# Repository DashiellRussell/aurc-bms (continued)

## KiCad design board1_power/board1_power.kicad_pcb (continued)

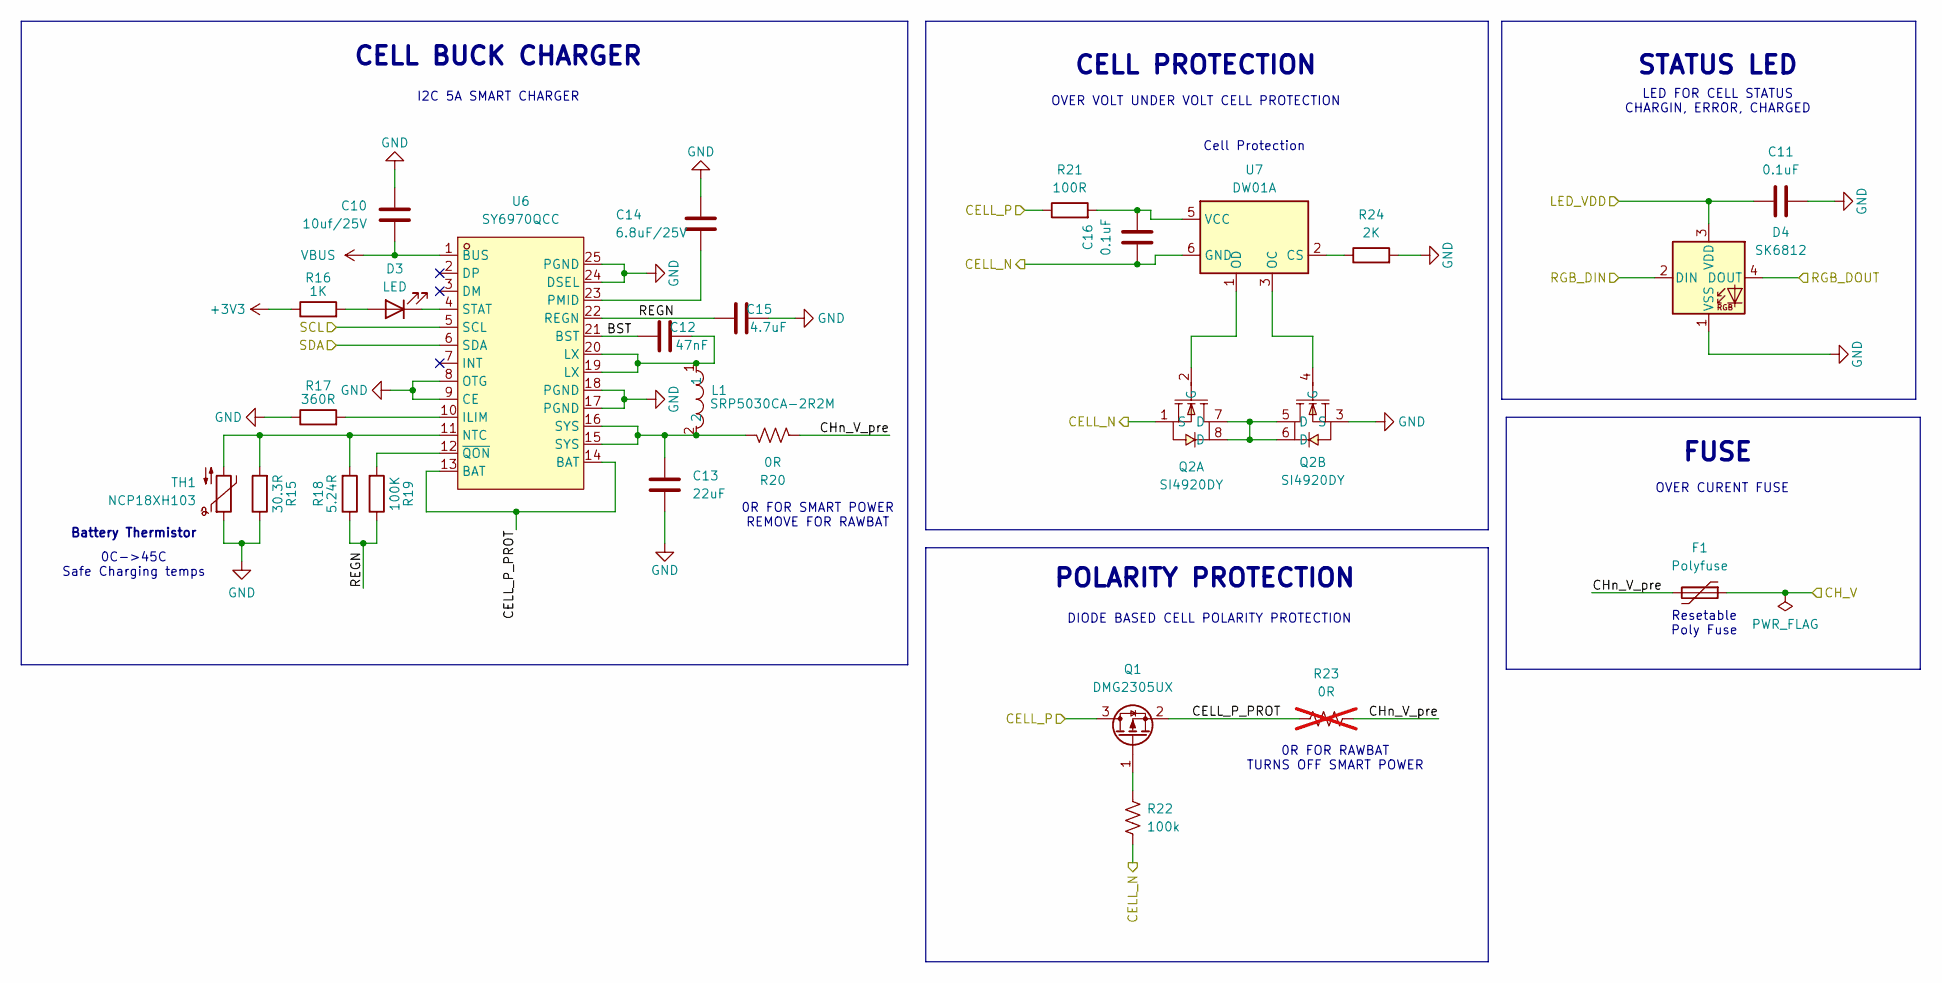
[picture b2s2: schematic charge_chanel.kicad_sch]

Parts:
C10: 10uf/25V; C_1206_3216Metric
C11, C16: 0.1uF; C_0603_1608Metric
C12: 47nF; C_0603_1608Metric
C13: 22uF; C_1206_3216Metric
C14: 6.8uF/25V; C_0805_2012Metric
C15: 4.7uF; C_0805_2012Metric
D3: LED; LED_0603_1608Metric
D4: SK6812; LED_SK6812_PLCC4_5.0x5.0mm_P3.2mm
F1: Polyfuse; Fuse_1812_4532Metric
L1: SRP5030CA-2R2M; IND-SMD_L5.5-W5.3; MPN SRP5030CA-2R2M; LCSC Part C2046809
Q1: DMG2305UX; SOT-23
Q2: SI4920DY; SOIC-8_L4.9-W3.9-P1.27-LS6.2-BL; MPN SI4920DY; LCSC Part C3289759
R15: 30.3R; R_0603_1608Metric
R16: 1K; R_0603_1608Metric
R17: 360R; R_0603_1608Metric
R18: 5.24R; R_0603_1608Metric
R19: 100K; R_0603_1608Metric
R20: 0R; R_2010_5025Metric
R21: 100R; R_0603_1608Metric
R22: 100k; R_0603_1608Metric
R23: 0R; R_2010_5025Metric; not fitted
R24: 2K; R_0603_1608Metric
TH1: NCP18XH103; R_0603_1608Metric
U6: SY6970QCC; QFN-24_L4.0-W4.0-P0.50-TL-EP2.7; MPN SY6970QCC; LCSC Part C5357542
U7: DW01A; SOT-23-6

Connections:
+3V3: R16.1; also elsewhere on the board
/CH1_CN: C16.1, Q2.1 (S), R22.1, U7.6 (GND); also elsewhere on the board
/CH1_CP: Q1.3 (D), R21.1; also elsewhere on the board
/CH1_SCL: U6.5 (SCL); also elsewhere on the board
/CH1_SDA: U6.6 (SDA); also elsewhere on the board
/CH1_V: C11.2, D4.3 (VDD), F1.1; also elsewhere on the board
/Charge_Chanel1 (FC1)/BST: C12.2, U6.21 (BST)
/Charge_Chanel1 (FC1)/CELL_P_PROT: Q1.2 (S), R23.2, U6.13 (BAT), U6.14 (BAT)
/Charge_Chanel1 (FC1)/CHn_V_pre: F1.2, R20.1, R23.1
/Charge_Chanel1 (FC1)/REGN: C15.2, R18.1, R19.1, U6.22 (REGN)
/Charge_Chanel1 (FC1)/RGB_DOUT: D4.4 (DOUT); also elsewhere on the board
/RGB_DATA: D4.2 (DIN); also elsewhere on the board
GND: C10.1, C11.1, C13.2, C14.1, C15.1, D4.1 (VSS), Q2.3 (S), R15.1, R17.1, R24.2, TH1.1, U6.8 (OTG), U6.9 (CE), U6.17 (PGND), U6.18 (PGND), U6.24 (DSEL), U6.25 (PGND); also elsewhere on the board
unnamed: C12.1, L1.1, U6.19 (LX), U6.20 (LX)
unnamed: C13.1, L1.2, R20.2, U6.15 (SYS), U6.16 (SYS)
unnamed: D3.2 (A), R16.2
unnamed: D3.1 (K), U6.4 (STAT)
unnamed: Q1.1 (G), R22.2
unnamed: Q2.5 (D), Q2.6 (D), Q2.7 (D), Q2.8 (D)
unnamed: Q2.2 (G), U7.1 (OD)
unnamed: Q2.4 (G), U7.3 (OC)
unnamed: R17.2, U6.10 (ILIM)
unnamed: R15.2, R18.2, TH1.2, U6.11 (NTC)
unnamed: C14.2, U6.23 (PMID)
unnamed: R19.2, U6.12 (~QON)
unnamed: R24.1, U7.2 (CS)
unnamed: C16.2, R21.2, U7.5 (VCC)
VBUS: C10.2, U6.1 (BUS); also elsewhere on the board

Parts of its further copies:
C17, C24, C31: 10uf/25V; C_1206_3216Metric
C18, C23, C25, C30, C32, C37: 0.1uF; C_0603_1608Metric
C19, C26, C33: 47nF; C_0603_1608Metric
C20, C27, C34: 22uF; C_1206_3216Metric
C21, C28, C35: 6.8uF/25V; C_0805_2012Metric
C22, C29, C36: 4.7uF; C_0805_2012Metric
D5, D7, D9: LED; LED_0603_1608Metric
D6, D8, D10: SK6812; LED_SK6812_PLCC4_5.0x5.0mm_P3.2mm
F2, F3, F4: Polyfuse; Fuse_1812_4532Metric
L2, L3, L4: SRP5030CA-2R2M; IND-SMD_L5.5-W5.3; MPN SRP5030CA-2R2M; LCSC Part C2046809
Q3, Q5, Q7: DMG2305UX; SOT-23
Q4, Q6, Q8: SI4920DY; SOIC-8_L4.9-W3.9-P1.27-LS6.2-BL; MPN SI4920DY; LCSC Part C3289759
R25, R35, R45: 30.3R; R_0603_1608Metric
R26, R36, R46: 1K; R_0603_1608Metric
R27, R37, R47: 360R; R_0603_1608Metric
R28, R38, R48: 5.24R; R_0603_1608Metric
R29, R39, R49: 100K; R_0603_1608Metric
R30, R40, R50: 0R; R_2010_5025Metric
R31, R41, R51: 100R; R_0603_1608Metric
R32, R42, R52: 100k; R_0603_1608Metric
R33, R43, R53: 0R; R_2010_5025Metric; not fitted
R34, R44, R54: 2K; R_0603_1608Metric
TH2, TH3, TH4: NCP18XH103; R_0603_1608Metric
U8, U10, U12: SY6970QCC; QFN-24_L4.0-W4.0-P0.50-TL-EP2.7; MPN SY6970QCC; LCSC Part C5357542
U9, U11, U13: DW01A; SOT-23-6

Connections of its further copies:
+3V3: R26.1, R36.1, R46.1; also elsewhere on the board
/CH1_V: C18.2, C25.2, C32.2, D6.3 (VDD), D8.3 (VDD), D10.3 (VDD); also elsewhere on the board
/CH2_CN: C23.1, Q4.1 (S), R32.1, U9.6 (GND); also elsewhere on the board
/CH2_CP: Q3.3 (D), R31.1; also elsewhere on the board
/CH2_SCL: U8.5 (SCL); also elsewhere on the board
/CH2_SDA: U8.6 (SDA); also elsewhere on the board
/CH2_V: F2.1; also elsewhere on the board
/CH3_CN: C30.1, Q6.1 (S), R42.1, U11.6 (GND); also elsewhere on the board
/CH3_CP: Q5.3 (D), R41.1; also elsewhere on the board
/CH3_SCL: U10.5 (SCL); also elsewhere on the board
/CH3_SDA: U10.6 (SDA); also elsewhere on the board
/CH3_V: F3.1; also elsewhere on the board
/CH4_CN: C37.1, Q8.1 (S), R52.1, U13.6 (GND); also elsewhere on the board
/CH4_CP: Q7.3 (D), R51.1; also elsewhere on the board
/CH4_SCL: U12.5 (SCL); also elsewhere on the board
/CH4_SDA: U12.6 (SDA); also elsewhere on the board
/CH4_V: F4.1; also elsewhere on the board
/Charge_Chanel1 (FC1)/RGB_DOUT: D6.2 (DIN); also elsewhere on the board
/Charge_Chanel2 (FC2)/BST: C19.2, U8.21 (BST)
/Charge_Chanel2 (FC2)/CELL_P_PROT: Q3.2 (S), R33.2, U8.13 (BAT), U8.14 (BAT)
/Charge_Chanel2 (FC2)/CHn_V_pre: F2.2, R30.1, R33.1
/Charge_Chanel2 (FC2)/REGN: C22.2, R28.1, R29.1, U8.22 (REGN)
/Charge_Chanel2 (FC2)/RGB_DOUT: D6.4 (DOUT), D8.2 (DIN)
/Charge_Chanel3(PYRO1)/BST: C26.2, U10.21 (BST)
/Charge_Chanel3(PYRO1)/CELL_P_PROT: Q5.2 (S), R43.2, U10.13 (BAT), U10.14 (BAT)
/Charge_Chanel3(PYRO1)/CHn_V_pre: F3.2, R40.1, R43.1
/Charge_Chanel3(PYRO1)/REGN: C29.2, R38.1, R39.1, U10.22 (REGN)
/Charge_Chanel3(PYRO1)/RGB_DOUT: D8.4 (DOUT), D10.2 (DIN)
/Charge_Chanel4(PYRO2)/BST: C33.2, U12.21 (BST)
/Charge_Chanel4(PYRO2)/CELL_P_PROT: Q7.2 (S), R53.2, U12.13 (BAT), U12.14 (BAT)
/Charge_Chanel4(PYRO2)/CHn_V_pre: F4.2, R50.1, R53.1
/Charge_Chanel4(PYRO2)/REGN: C36.2, R48.1, R49.1, U12.22 (REGN)
/Charge_Chanel4(PYRO2)/RGB_DOUT: D10.4 (DOUT)
GND: C17.1, C18.1, C20.2, C21.1, C22.1, C24.1, C25.1, C27.2, C28.1, C29.1, C31.1, C32.1, C34.2, C35.1, C36.1, D6.1 (VSS), D8.1 (VSS), D10.1 (VSS), Q4.3 (S), Q6.3 (S), Q8.3 (S), R25.1, R27.1, R34.2, R35.1, R37.1, R44.2, R45.1, R47.1, R54.2, TH2.1, TH3.1, TH4.1, U8.8 (OTG), U8.9 (CE), U8.17 (PGND), U8.18 (PGND), U8.24 (DSEL), U8.25 (PGND), U10.8 (OTG), U10.9 (CE), U10.17 (PGND), U10.18 (PGND), U10.24 (DSEL), U10.25 (PGND), U12.8 (OTG), U12.9 (CE), U12.17 (PGND), U12.18 (PGND), U12.24 (DSEL), U12.25 (PGND); also elsewhere on the board
unnamed: C19.1, L2.1, U8.19 (LX), U8.20 (LX)
unnamed: C20.1, L2.2, R30.2, U8.15 (SYS), U8.16 (SYS)
unnamed: C26.1, L3.1, U10.19 (LX), U10.20 (LX)
unnamed: C27.1, L3.2, R40.2, U10.15 (SYS), U10.16 (SYS)
unnamed: C33.1, L4.1, U12.19 (LX), U12.20 (LX)
unnamed: C34.1, L4.2, R50.2, U12.15 (SYS), U12.16 (SYS)
unnamed: D5.2 (A), R26.2
unnamed: D5.1 (K), U8.4 (STAT)
unnamed: D7.2 (A), R36.2
unnamed: D7.1 (K), U10.4 (STAT)
unnamed: D9.2 (A), R46.2
unnamed: D9.1 (K), U12.4 (STAT)
unnamed: Q3.1 (G), R32.2
unnamed: Q4.5 (D), Q4.6 (D), Q4.7 (D), Q4.8 (D)
unnamed: Q4.2 (G), U9.1 (OD)
unnamed: Q4.4 (G), U9.3 (OC)
unnamed: Q5.1 (G), R42.2
unnamed: Q6.5 (D), Q6.6 (D), Q6.7 (D), Q6.8 (D)
unnamed: Q6.2 (G), U11.1 (OD)
unnamed: Q6.4 (G), U11.3 (OC)
unnamed: Q7.1 (G), R52.2
unnamed: Q8.5 (D), Q8.6 (D), Q8.7 (D), Q8.8 (D)
unnamed: Q8.2 (G), U13.1 (OD)
unnamed: Q8.4 (G), U13.3 (OC)
unnamed: R27.2, U8.10 (ILIM)
unnamed: R25.2, R28.2, TH2.2, U8.11 (NTC)
unnamed: C21.2, U8.23 (PMID)
unnamed: R29.2, U8.12 (~QON)
unnamed: R34.1, U9.2 (CS)
unnamed: C23.2, R31.2, U9.5 (VCC)
unnamed: R37.2, U10.10 (ILIM)
unnamed: R35.2, R38.2, TH3.2, U10.11 (NTC)
unnamed: C28.2, U10.23 (PMID)
unnamed: R39.2, U10.12 (~QON)
unnamed: R44.1, U11.2 (CS)
unnamed: C30.2, R41.2, U11.5 (VCC)
unnamed: R47.2, U12.10 (ILIM)
unnamed: R45.2, R48.2, TH4.2, U12.11 (NTC)
unnamed: C35.2, U12.23 (PMID)
unnamed: R49.2, U12.12 (~QON)
unnamed: R54.1, U13.2 (CS)
unnamed: C37.2, R51.2, U13.5 (VCC)
VBUS: C17.2, C24.2, C31.2, U8.1 (BUS), U10.1 (BUS), U12.1 (BUS); also elsewhere on the board

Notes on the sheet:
OVER VOLT UNDER VOLT CELL PROTECTION
CELL PROTECTION
0R FOR RAWBAT TURNS OFF SMART POWER
POLARITY PROTECTION
STATUS LED
Battery Thermistor
0C->45C Safe Charging temps
0R FOR SMART POWER REMOVE FOR RAWBAT
OVER CURENT FUSE
FUSE
Cell Protection
DIODE BASED CELL POLARITY PROTECTION
I2C 5A SMART CHARGER
CELL BUCK CHARGER
LED FOR CELL STATUS CHARGIN, ERROR, CHARGED
Resetable Poly Fuse

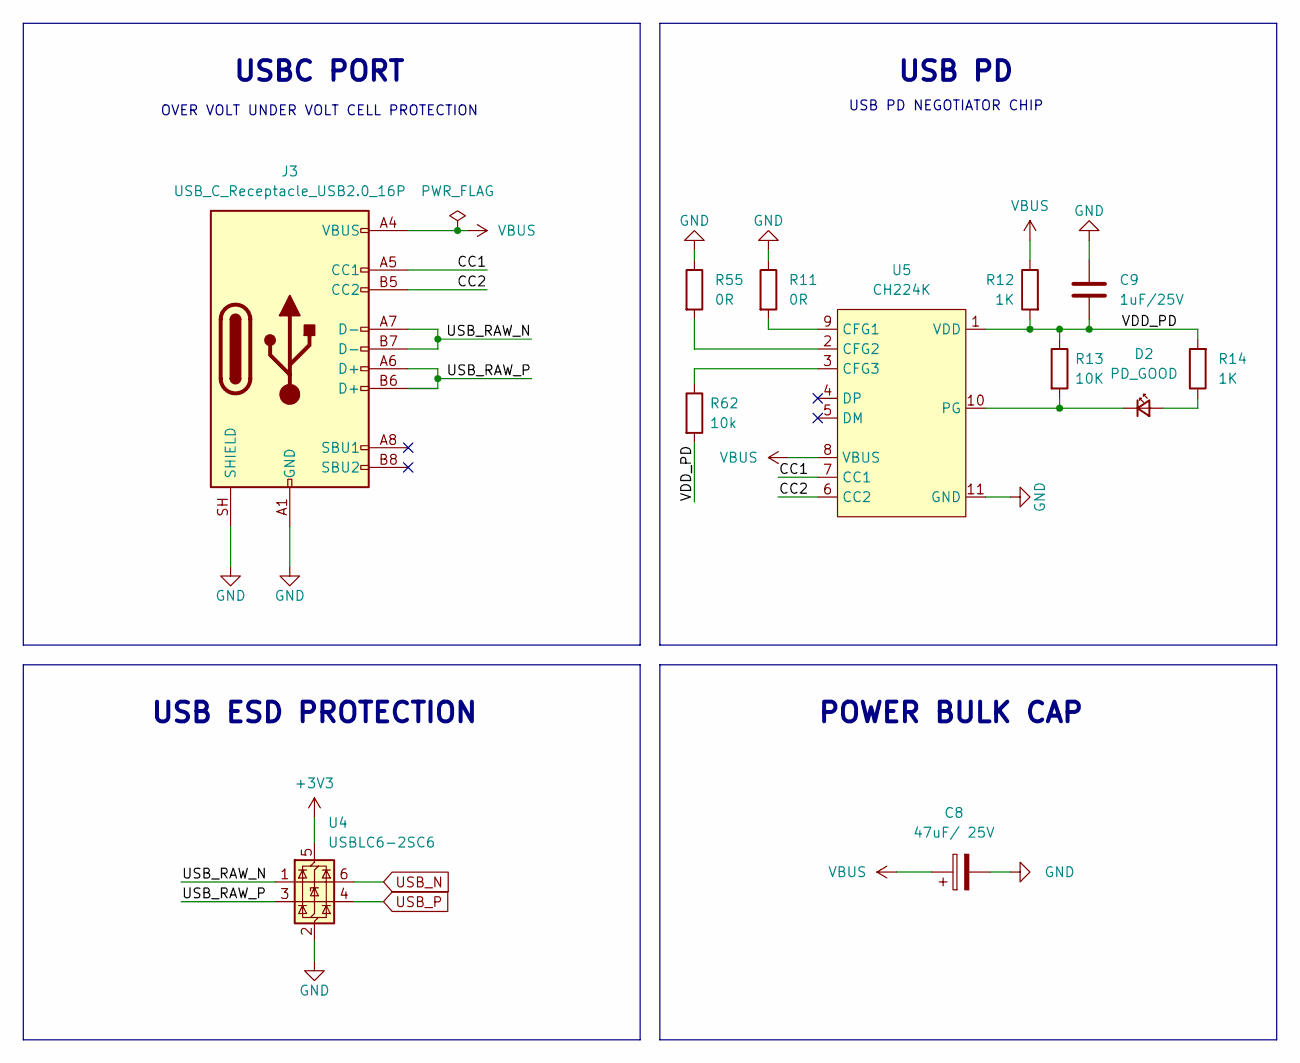
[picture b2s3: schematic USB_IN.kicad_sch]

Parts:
C8: 47uF/ 25V; CP_Elec_6.3x5.4
C9: 1uF/25V; C_0603_1608Metric
D2: PD_GOOD; LED_0603_1608Metric_Green
J3: USB_C_Receptacle_USB2.0_16P; USB_C_Receptacle_GCT_USB4105-xx-A_16P_TopMnt_Horizontal
R11, R55: 0R; R_0805_2012Metric
R12: 1K; R_0805_2012Metric
R13: 10K; R_0603_1608Metric
R14: 1K; R_0603_1608Metric
R62: 10k; R_0805_2012Metric
U4: USBLC6-2SC6; SOT-23-6
U5: CH224K; ESSOP-10_L4.9-W3.9-P1.0-LS6.0-TL-EP; MPN CH224K; LCSC Part C970725

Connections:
+3V3: U4.5 (VBUS); also elsewhere on the board
/USB_IN/CC1: J3.A5 (CC1), U5.7 (CC1)
/USB_IN/CC2: J3.B5 (CC2), U5.6 (CC2)
/USB_IN/USB_RAW_N: J3.A7 (D-), J3.B7 (D-), U4.1 (I/O1)
/USB_IN/USB_RAW_P: J3.A6 (D+), J3.B6 (D+), U4.3 (I/O2)
/USB_IN/VDD_PD: C9.2, R12.2, R13.1, R14.2, R62.2, U5.1 (VDD)
GND: C8.2, C9.1, J3.A1 (GND), J3.A12 (GND), J3.B1 (GND), J3.B12 (GND), J3.SH (SHIELD), R11.1, R55.1, U4.2 (GND), U5.11 (GND); also elsewhere on the board
unnamed: D2.2 (A), R14.1
unnamed: D2.1 (K), R13.2, U5.10 (PG)
unnamed: R11.2, U5.9 (CFG1)
unnamed: R55.2, U5.2 (CFG2)
unnamed: R62.1, U5.3 (CFG3)
USB_N: U4.6 (I/O1); also elsewhere on the board
USB_P: U4.4 (I/O2); also elsewhere on the board
VBUS: C8.1, J3.A4 (VBUS), J3.A9 (VBUS), J3.B4 (VBUS), J3.B9 (VBUS), R12.1, U5.8 (VBUS); also elsewhere on the board

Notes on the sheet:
OVER VOLT UNDER VOLT CELL PROTECTION
USB ESD PROTECTION
USBC PORT
USB PD
POWER BULK CAP
USB PD NEGOTIATOR CHIP

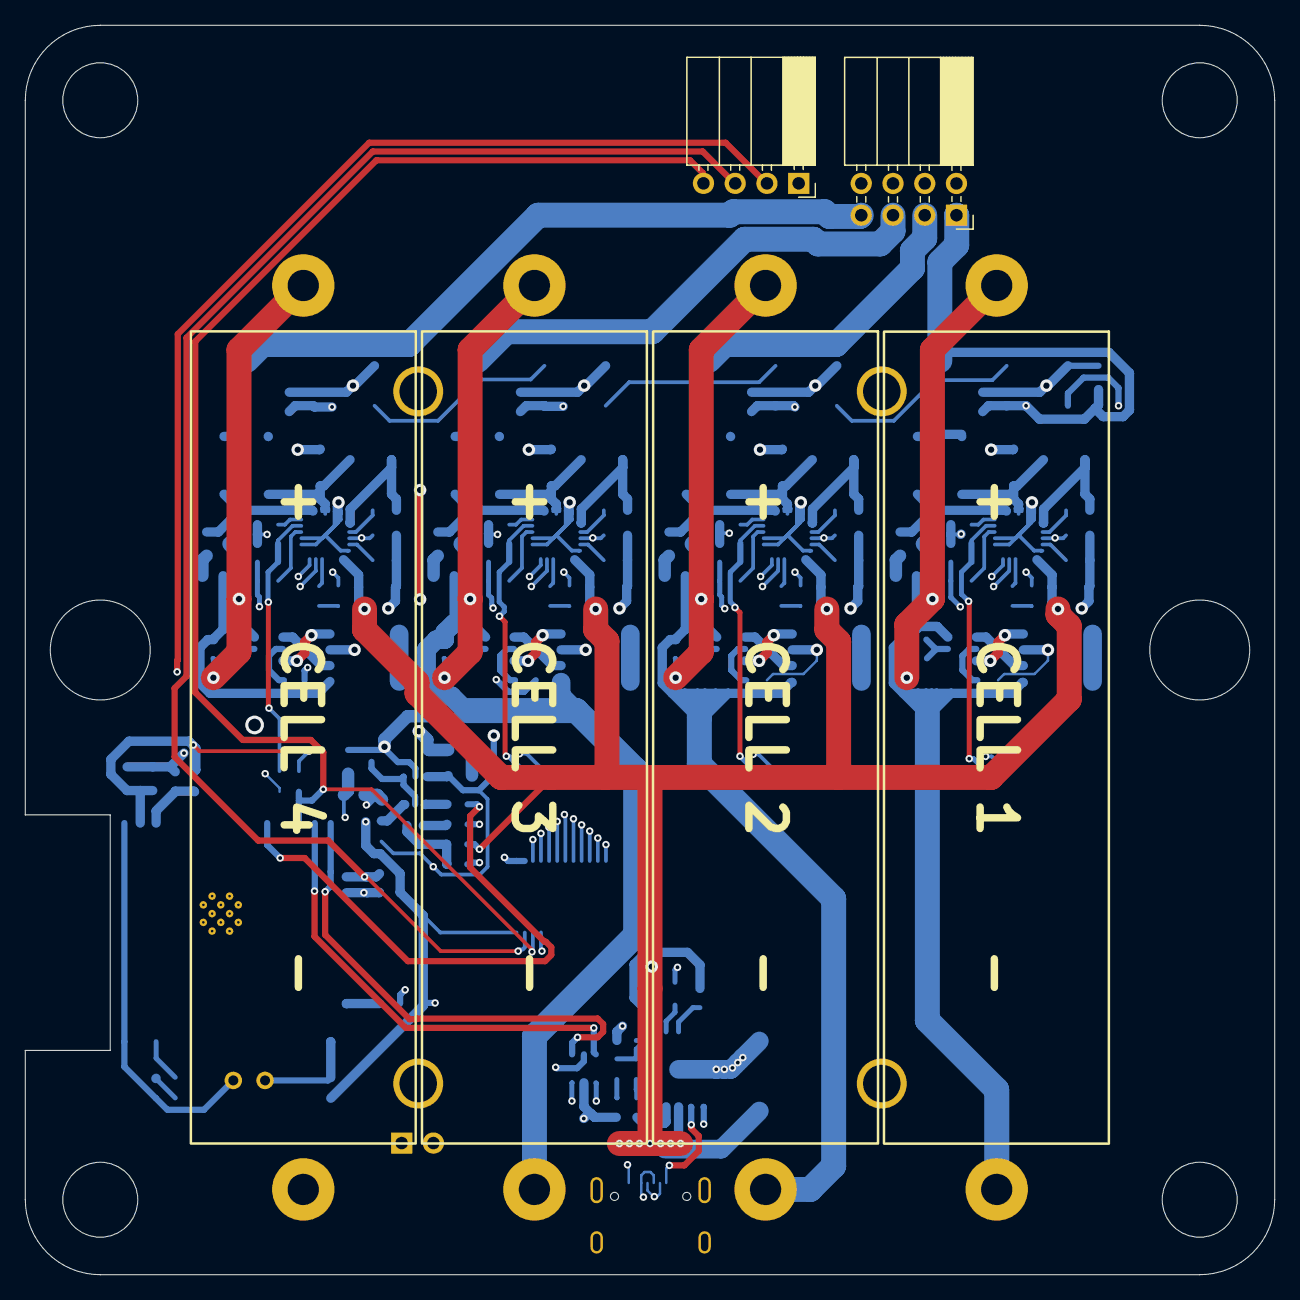
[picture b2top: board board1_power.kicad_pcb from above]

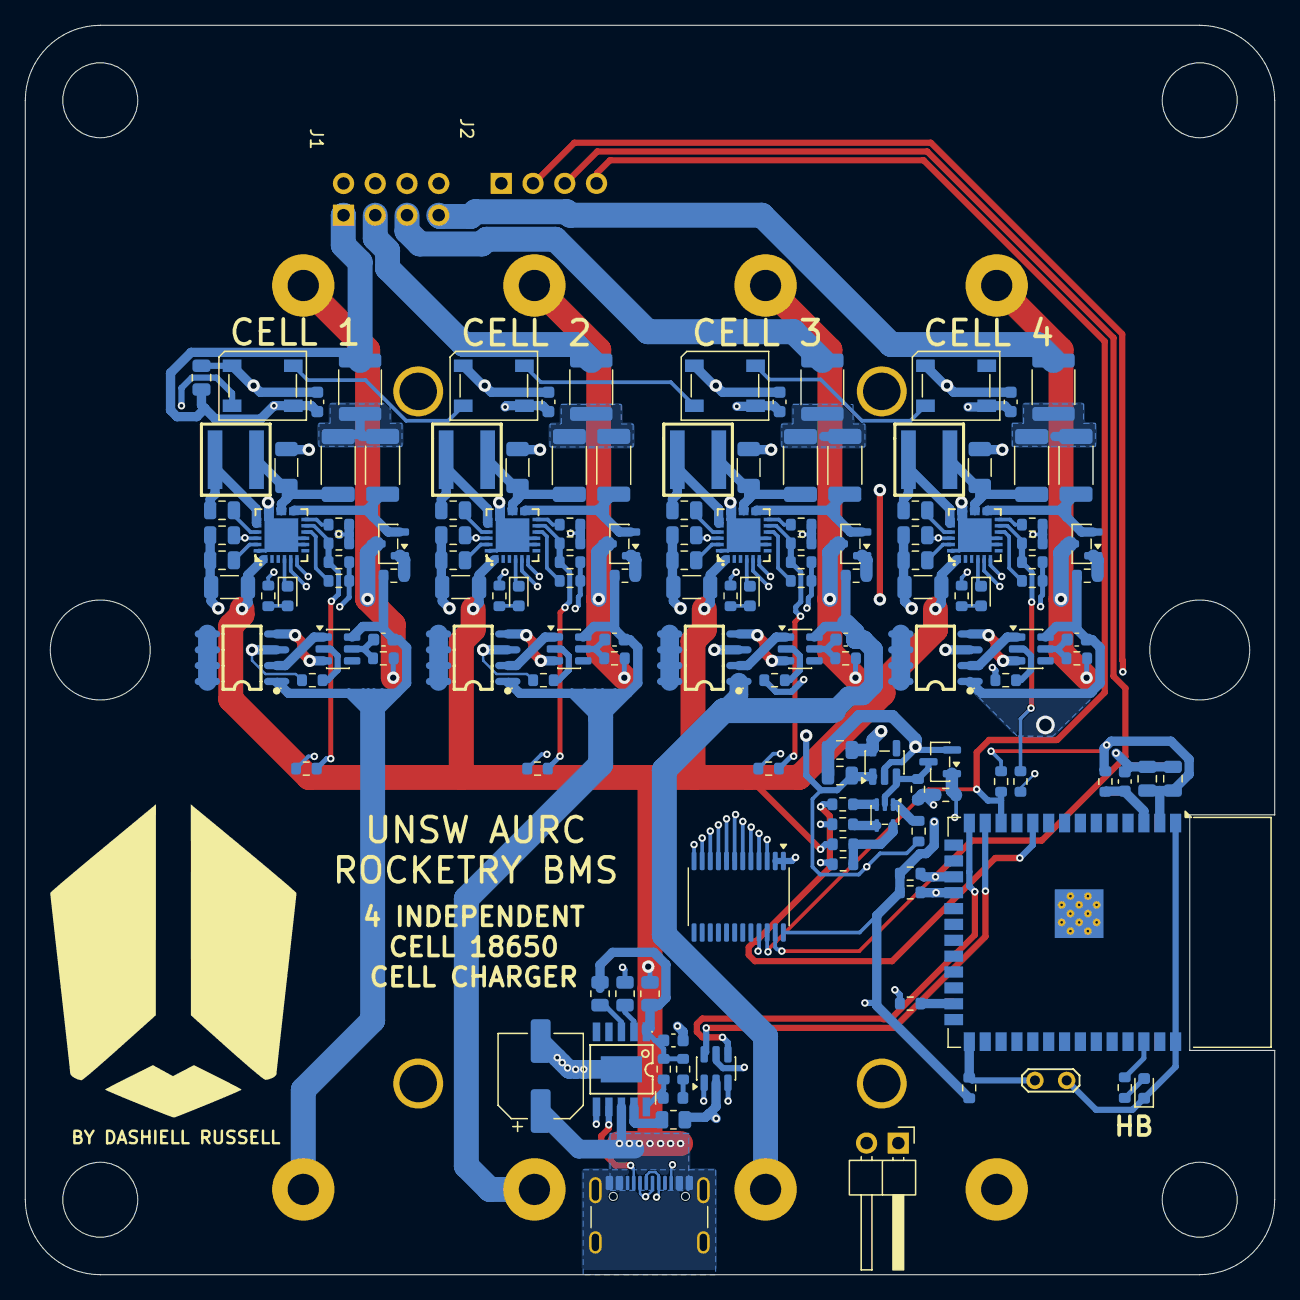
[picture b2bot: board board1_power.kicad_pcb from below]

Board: 4 copper layers, 100.0 x 100.0 mm, 147 parts (144 on the bottom side), 127 nets.

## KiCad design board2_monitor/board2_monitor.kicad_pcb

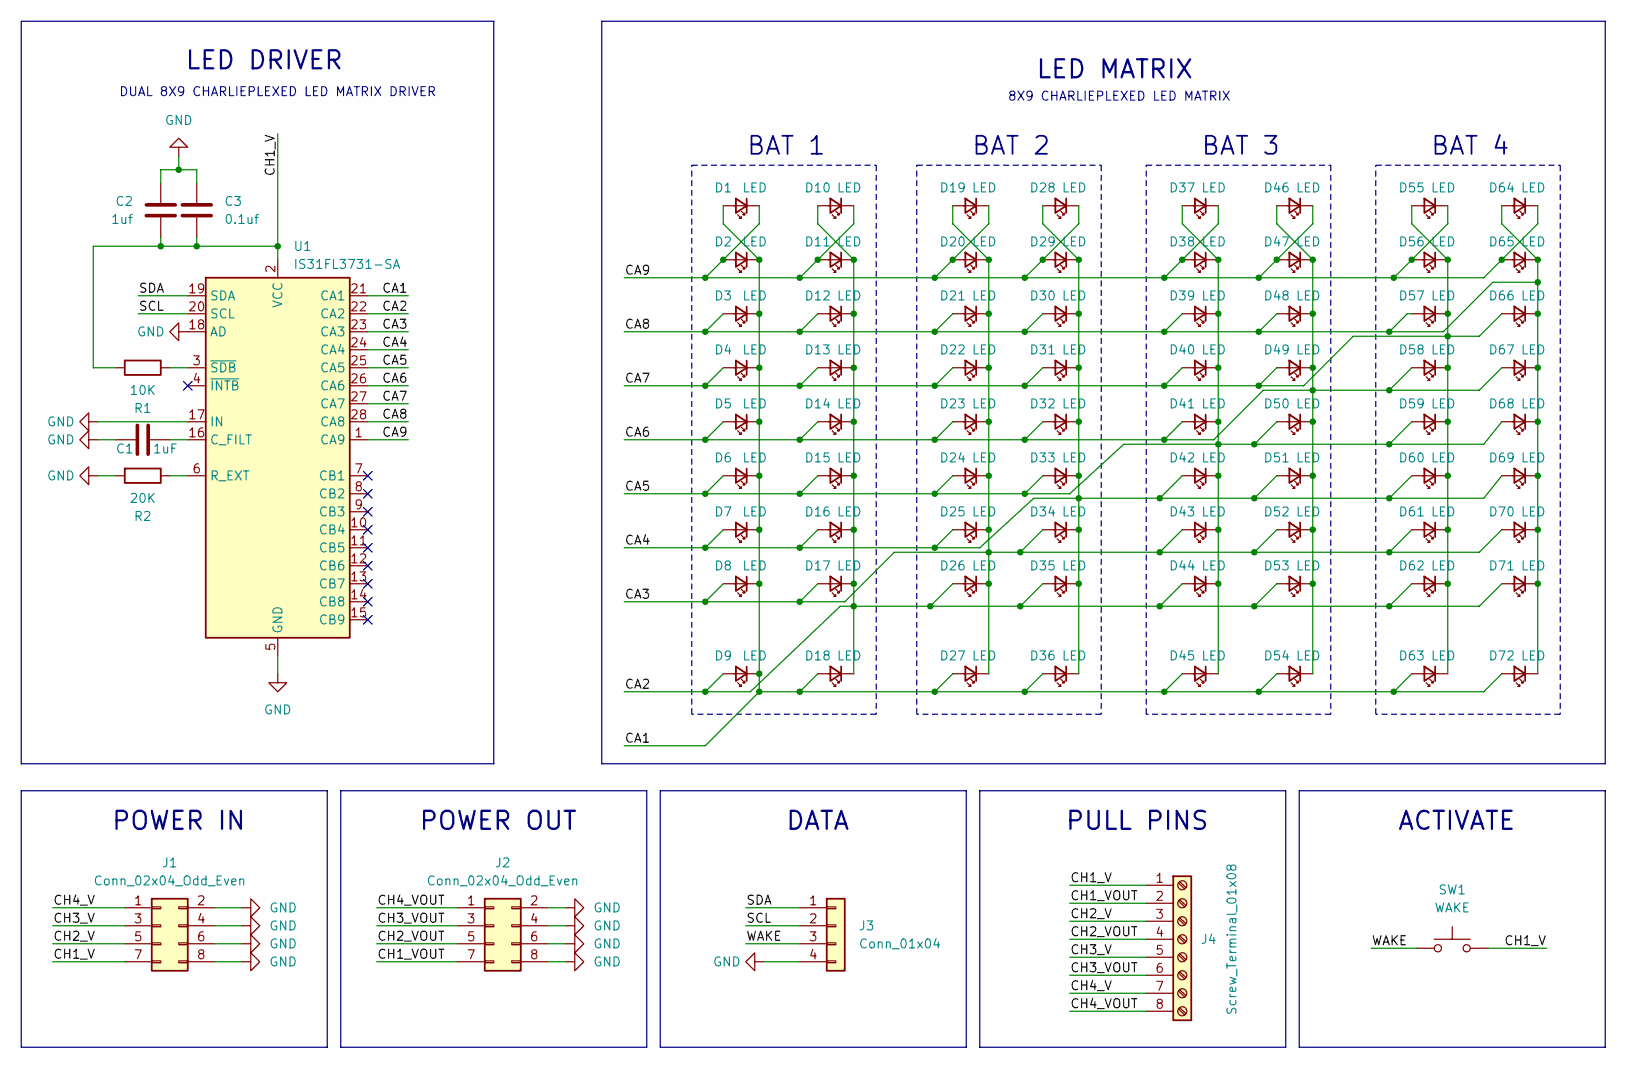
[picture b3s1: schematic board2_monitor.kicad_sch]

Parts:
C1: 1uF; C_0805_2012Metric
C2: 1uf; C_0805_2012Metric
C3: 0.1uf; C_0805_2012Metric
D1, D2, D3, D4, D5, D6, D7, D8, D9, D10, D11, D12, D13, D14, D15, D16, D17, D18, D19, D20, D21, D22, D23, D24, D25, D26, D27, D28, D29, D30, D31, D32, D33, D34, D35, D36, D37, D38, D39, D40, D41, D42, D43, D44, D45, D46, D47, D48, D49, D50, D51, D52, D53, D54, D55, D56, D57, D58, D59, D60, D61, D62, D63, D64, D65, D66, D67, D68, D69, D70, D71, D72: LED; LED_0603_1608Metric
J1, J2: Conn_02x04_Odd_Even; PinHeader_2x04_P2.54mm_Vertical
J3: Conn_01x04; PinHeader_1x04_P2.54mm_Vertical
J4: Screw_Terminal_01x08; TerminalBlock_Phoenix_PT-1,5-8-3.5-H_1x08_P3.50mm_Horizontal
R1: 10K; R_0805_2012Metric
R2: 20K; R_0805_2012Metric
SW1: WAKE; SW_Push_1P1T_NO_CK_KMR2
U1: IS31FL3731-SA; SSOP-28_5.3x10.2mm_P0.65mm

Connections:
/CA1: D1.2 (A), D2.1 (K), D3.1 (K), D4.1 (K), D5.1 (K), D6.1 (K), D7.1 (K), D8.1 (K), D9.1 (K), D18.2 (A), D27.2 (A), D36.2 (A), D45.2 (A), D54.2 (A), D63.2 (A), D72.2 (A), U1.21 (CA1)
/CA2: D9.2 (A), D10.2 (A), D11.1 (K), D12.1 (K), D13.1 (K), D14.1 (K), D15.1 (K), D16.1 (K), D17.1 (K), D18.1 (K), D26.2 (A), D35.2 (A), D44.2 (A), D53.2 (A), D62.2 (A), D71.2 (A), U1.22 (CA2)
/CA3: D8.2 (A), D17.2 (A), D19.2 (A), D20.1 (K), D21.1 (K), D22.1 (K), D23.1 (K), D24.1 (K), D25.1 (K), D26.1 (K), D27.1 (K), D34.2 (A), D43.2 (A), D52.2 (A), D61.2 (A), D70.2 (A), U1.23 (CA3)
/CA4: D7.2 (A), D16.2 (A), D25.2 (A), D28.2 (A), D29.1 (K), D30.1 (K), D31.1 (K), D32.1 (K), D33.1 (K), D34.1 (K), D35.1 (K), D36.1 (K), D42.2 (A), D51.2 (A), D60.2 (A), D69.2 (A), U1.24 (CA4)
/CA5: D6.2 (A), D15.2 (A), D24.2 (A), D33.2 (A), D37.2 (A), D38.1 (K), D39.1 (K), D40.1 (K), D41.1 (K), D42.1 (K), D43.1 (K), D44.1 (K), D45.1 (K), D50.2 (A), D59.2 (A), D68.2 (A), U1.25 (CA5)
/CA6: D5.2 (A), D14.2 (A), D23.2 (A), D32.2 (A), D41.2 (A), D46.2 (A), D47.1 (K), D48.1 (K), D49.1 (K), D50.1 (K), D51.1 (K), D52.1 (K), D53.1 (K), D54.1 (K), D58.2 (A), D67.2 (A), U1.26 (CA6)
/CA7: D4.2 (A), D13.2 (A), D22.2 (A), D31.2 (A), D40.2 (A), D49.2 (A), D55.2 (A), D56.1 (K), D57.1 (K), D58.1 (K), D59.1 (K), D60.1 (K), D61.1 (K), D62.1 (K), D63.1 (K), D66.2 (A), U1.27 (CA7)
/CA8: D3.2 (A), D12.2 (A), D21.2 (A), D30.2 (A), D39.2 (A), D48.2 (A), D57.2 (A), D64.2 (A), D65.1 (K), D66.1 (K), D67.1 (K), D68.1 (K), D69.1 (K), D70.1 (K), D71.1 (K), D72.1 (K), U1.28 (CA8)
/CA9: D1.1 (K), D2.2 (A), D10.1 (K), D11.2 (A), D19.1 (K), D20.2 (A), D28.1 (K), D29.2 (A), D37.1 (K), D38.2 (A), D46.1 (K), D47.2 (A), D55.1 (K), D56.2 (A), D64.1 (K), D65.2 (A), U1.1 (CA9)
/CH1_V: C2.1, C3.1, J1.7, J4.1, R1.2, SW1.2, U1.2 (VCC)
/CH1_VOUT: J2.7, J4.2
/CH2_V: J1.5, J4.3
/CH2_VOUT: J2.5, J4.4
/CH3_V: J1.3, J4.5
/CH3_VOUT: J2.3, J4.6
/CH4_V: J1.1, J4.7
/CH4_VOUT: J2.1, J4.8
/SCL: J3.2, U1.20 (SCL)
/SDA: J3.1, U1.19 (SDA)
/WAKE: J3.3, SW1.1
GND: C1.2, C2.2, C3.2, J1.2, J1.4, J1.6, J1.8, J2.2, J2.4, J2.6, J2.8, J3.4, R2.2, U1.5 (GND), U1.17 (IN), U1.18 (AD)
unnamed: C1.1, U1.16 (C_FILT)
unnamed: R2.1, U1.6 (R_EXT)
unnamed: R1.1, U1.3 (~SDB)

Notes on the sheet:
BAT 1
8X9 CHARLIEPLEXED LED MATRIX
BAT 4
LED MATRIX
LED DRIVER
BAT 2
PULL PINS
ACTIVATE
POWER OUT
POWER IN
DATA
DUAL 8X9 CHARLIEPLEXED LED MATRIX DRIVER
BAT 3

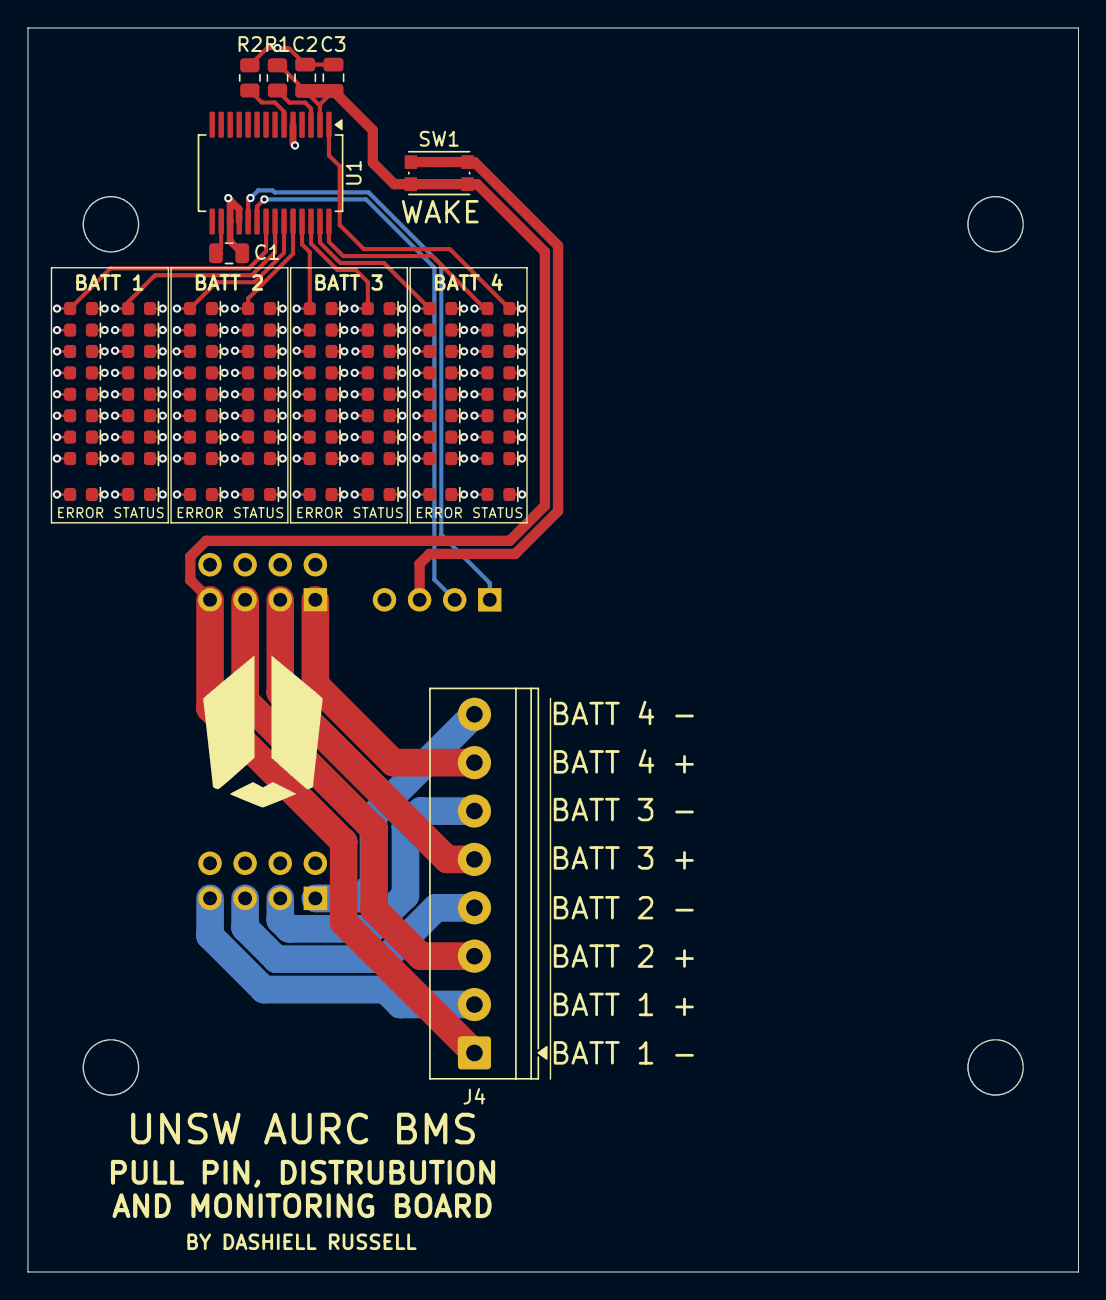
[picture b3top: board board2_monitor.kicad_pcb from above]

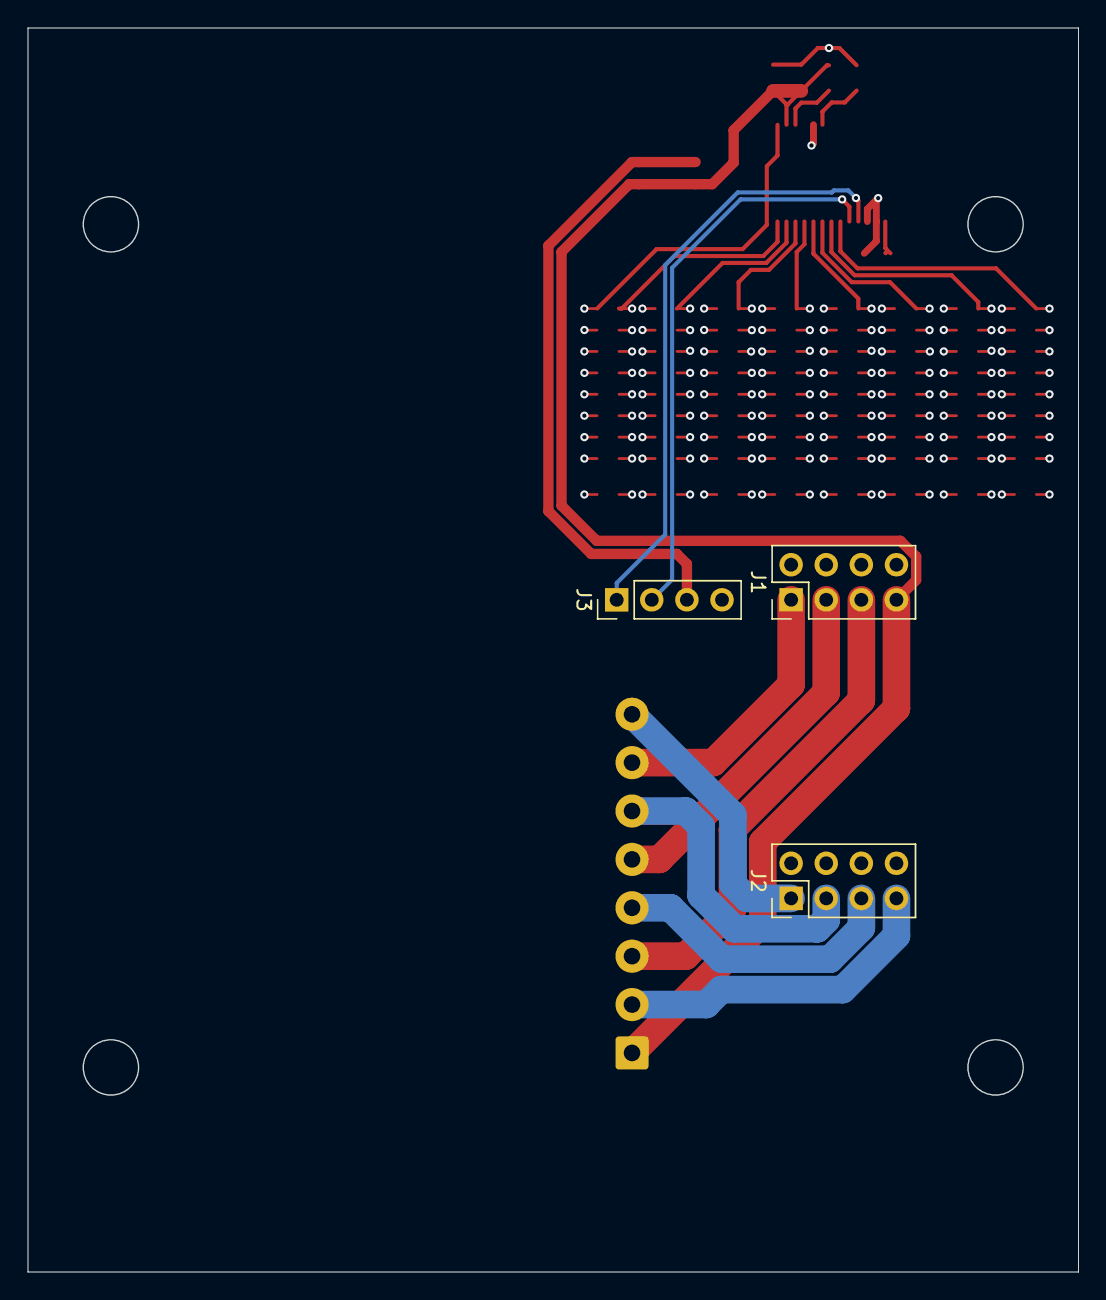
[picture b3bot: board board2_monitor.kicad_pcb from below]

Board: 4 copper layers, 76.0 x 90.0 mm, 83 parts (3 on the bottom side), 24 nets.

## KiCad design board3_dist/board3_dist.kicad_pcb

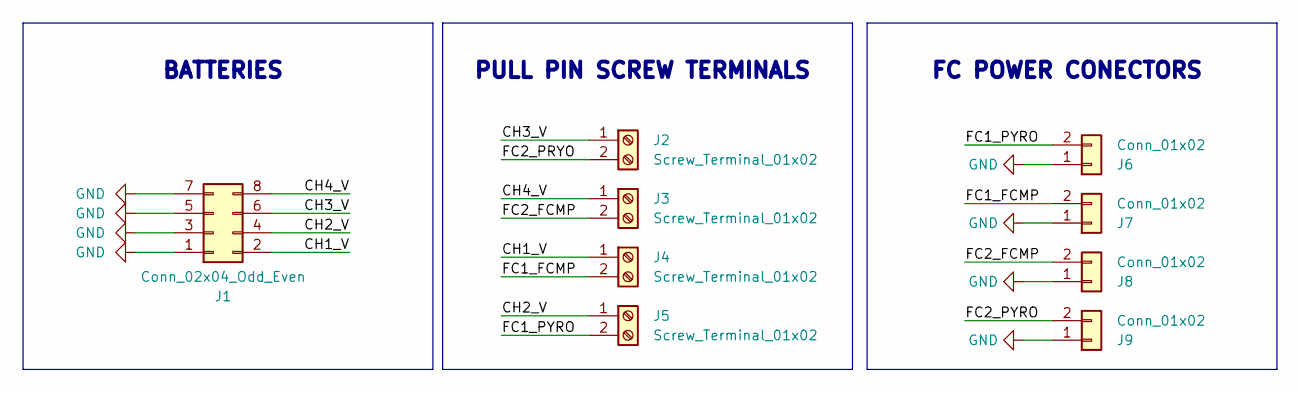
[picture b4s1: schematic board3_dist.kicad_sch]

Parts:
J1: Conn_02x04_Odd_Even; PinSocket_2x04_P2.54mm_Horizontal
J2, J3, J4, J5: Screw_Terminal_01x02; TerminalBlock_Phoenix_PT-1,5-2-3.5-H_1x02_P3.50mm_Horizontal
J6, J7, J8, J9: Conn_01x02; PinSocket_1x02_P2.54mm_Horizontal

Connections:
/CH1_V: J1.2, J4.1
/CH2_V: J1.4, J5.1
/CH3_V: J1.6, J2.1
/CH4_V: J1.8, J3.1
/FC1_FCMP: J4.2, J7.2
/FC1_PYRO: J5.2, J6.2
/FC2_FCMP: J3.2, J8.2
/FC2_PRYO: J2.2
/FC2_PYRO: J9.2
GND: J1.1, J1.3, J1.5, J1.7, J6.1, J7.1, J8.1, J9.1

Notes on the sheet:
FC POWER CONECTORS
PULL PIN SCREW TERMINALS
BATTERIES

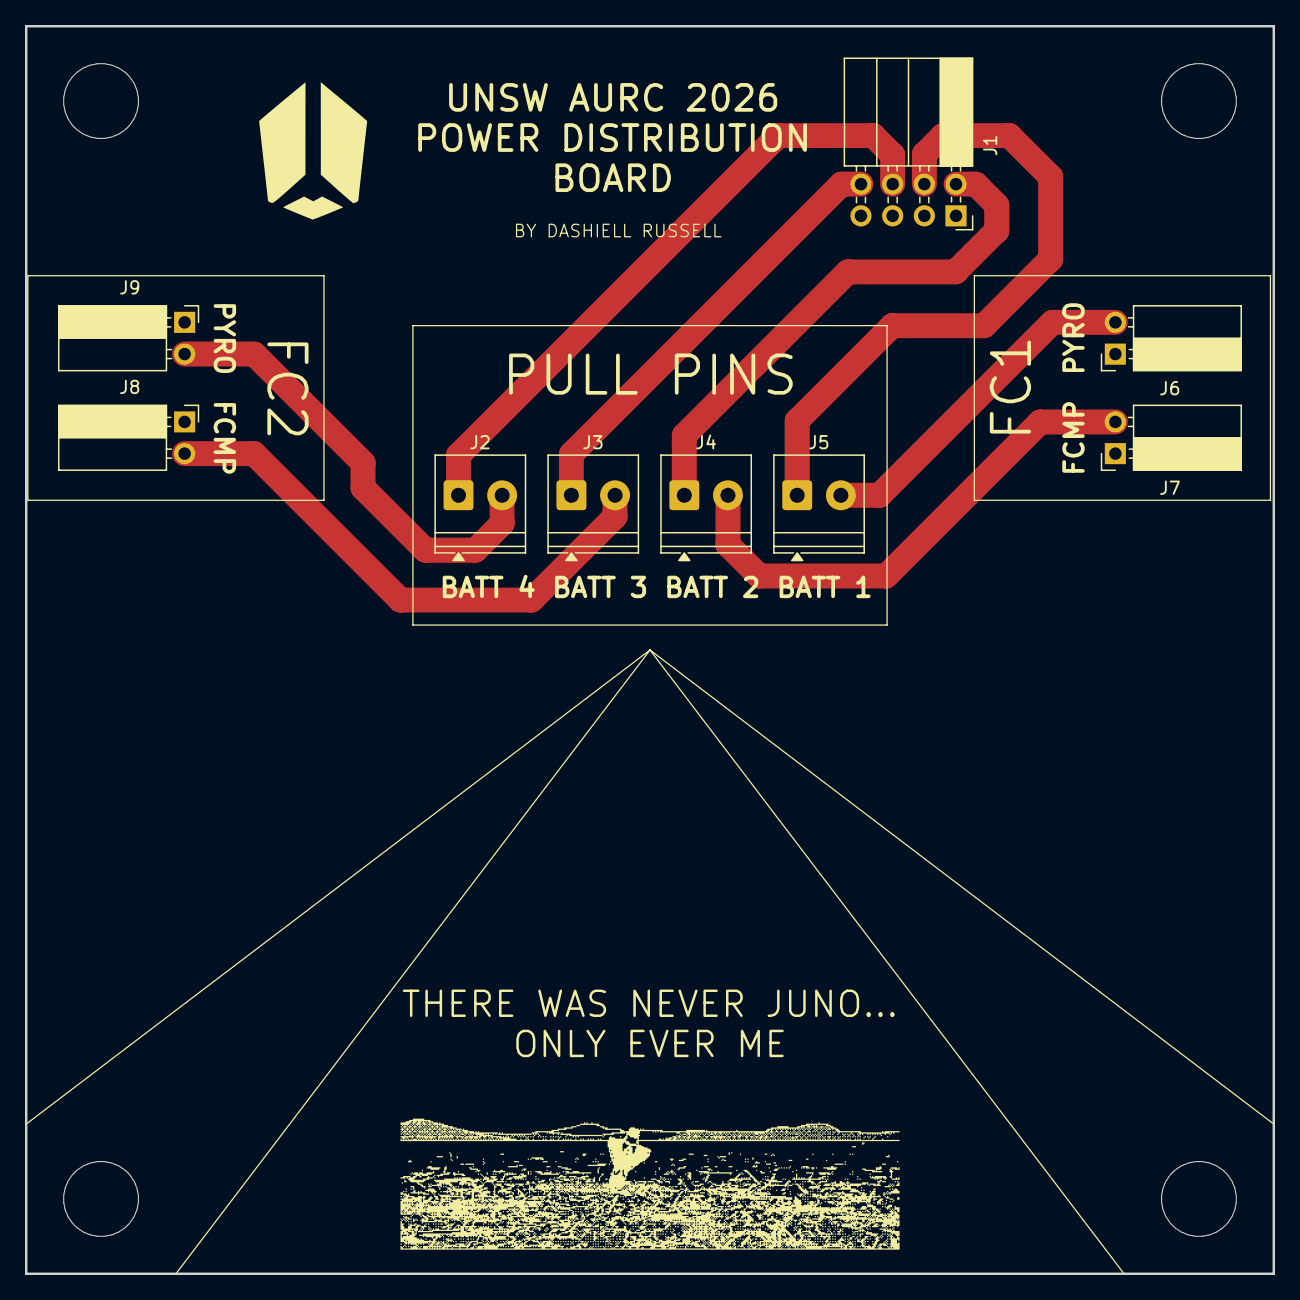
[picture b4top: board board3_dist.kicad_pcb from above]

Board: 2 copper layers, 100.0 x 100.0 mm, 9 parts (0 on the bottom side), 8 nets.
